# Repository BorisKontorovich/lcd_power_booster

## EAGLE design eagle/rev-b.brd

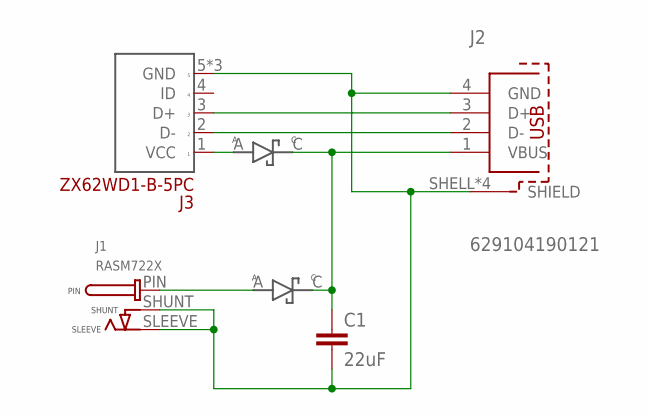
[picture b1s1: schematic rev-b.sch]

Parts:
C1: 22uF; 1206
D1, D2: PMEG6030ETP; SOD128
J1: RASM722X; SWITCHCRAFT_RASM722X
J2: 629104190121
J3: ZX62WD1-B-5PC

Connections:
unnamed: J2.3 (D+), J3.3 (D+)
unnamed: J2.2 (D-), J3.2 (D-)
unnamed: C1.1, D1.C, D2.C, J2.1 (VBUS)
unnamed: D2.A, J3.1 (VCC)
unnamed: D1.A, J1.PIN
unnamed: C1.2, J1.SHUNT, J1.SLEEVE, J2.4 (GND), J2.SHELL (SHIELD), J2.SHELL1 (SHIELD), J2.SHELL2 (SHIELD), J2.SHELL3 (SHIELD), J3.5 (GND), J3.P$1 (GND), J3.P$2 (GND)

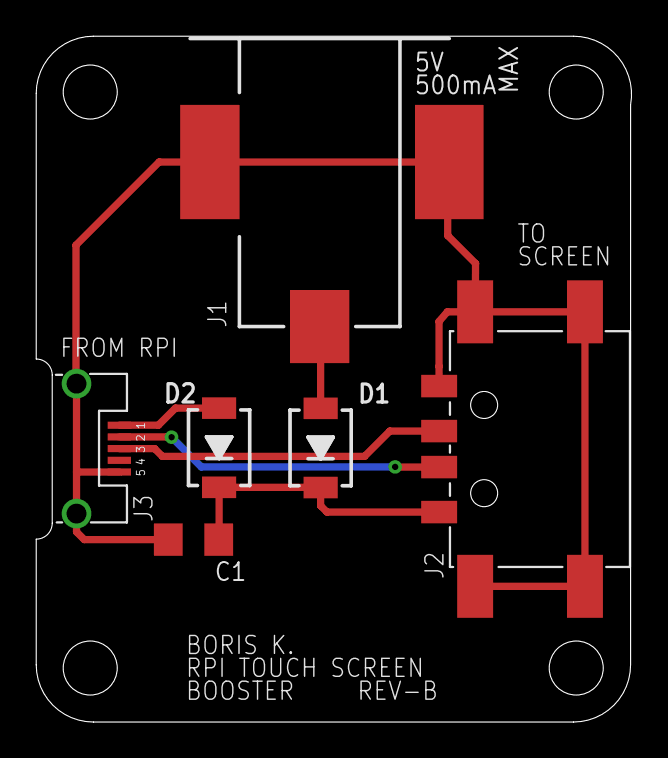
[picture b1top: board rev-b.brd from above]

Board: 2 copper layers, 33.1 x 38.1 mm, 6 parts (0 on the bottom side), 6 nets.

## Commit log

2018-06-10 Adding new files

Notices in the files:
parts and their libraries:
SparkFun-Capacitors: Licensing: Creative Commons ShareAlike 4.0 International - https://creativecommons.org/licenses/by-sa/4.0
